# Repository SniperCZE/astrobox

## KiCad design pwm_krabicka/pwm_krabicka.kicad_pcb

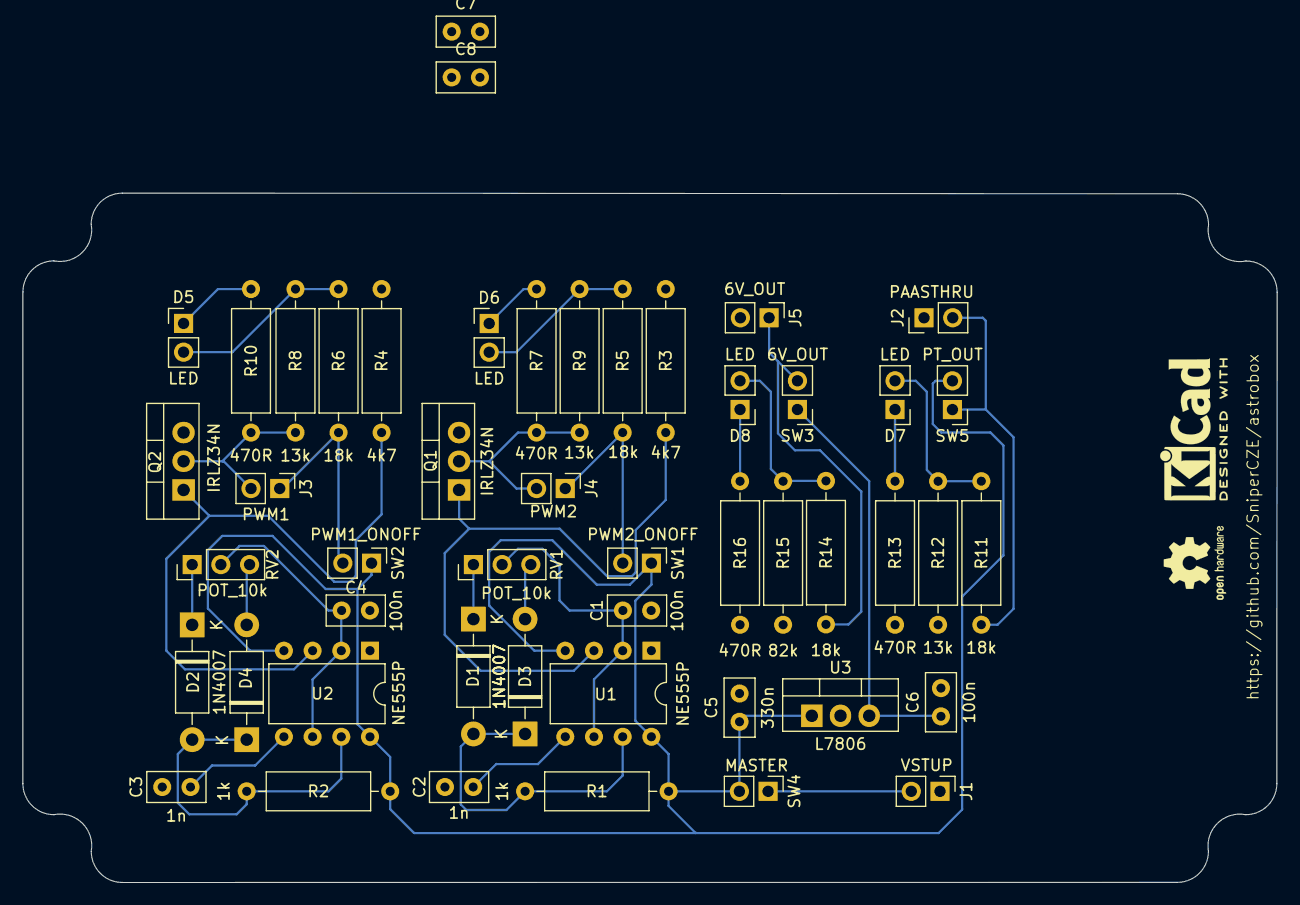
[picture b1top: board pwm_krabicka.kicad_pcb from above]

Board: 2 copper layers, 111.0 x 61.0 mm, 49 parts (0 on the bottom side), 30 nets.

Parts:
C1, C4, C6, C8: 100n; C_Disc_D5.0mm_W2.5mm_P2.50mm
C2, C3: 1n; C_Disc_D5.0mm_W2.5mm_P2.50mm
C5, C7: 330n; C_Disc_D5.0mm_W2.5mm_P2.50mm
D1, D2, D3, D4: 1N4007; D_DO-41_SOD81_P10.16mm_Horizontal
D5, D6, D7, D8: LED; PinHeader_1x02_P2.54mm_Vertical
J1: VSTUP; PinHeader_1x02_P2.54mm_Vertical
J2: PAASTHRU; PinHeader_1x02_P2.54mm_Vertical
J3: PWM1; PinHeader_1x02_P2.54mm_Vertical
J4: PWM2; PinHeader_1x02_P2.54mm_Vertical
J5: 6V_OUT; PinHeader_1x02_P2.54mm_Vertical
Q1, Q2: IRLZ34N; TO-220-3_Vertical
R1, R2: 1k; R_Axial_DIN0309_L9.0mm_D3.2mm_P12.70mm_Horizontal
R3, R4: 4k7; R_Axial_DIN0309_L9.0mm_D3.2mm_P12.70mm_Horizontal
R5, R6, R11, R14: 18k; R_Axial_DIN0309_L9.0mm_D3.2mm_P12.70mm_Horizontal
R7, R10, R13, R16: 470R; R_Axial_DIN0309_L9.0mm_D3.2mm_P12.70mm_Horizontal
R8, R9, R12: 13k; R_Axial_DIN0309_L9.0mm_D3.2mm_P12.70mm_Horizontal
R15: 82k; R_Axial_DIN0309_L9.0mm_D3.2mm_P12.70mm_Horizontal
RV1, RV2: POT_10k; PinHeader_1x03_P2.54mm_Vertical
SW1: PWM2_ONOFF; PinHeader_1x02_P2.54mm_Vertical
SW2: PWM1_ONOFF; PinHeader_1x02_P2.54mm_Vertical
SW3: 6V_OUT; PinHeader_1x02_P2.54mm_Vertical
SW4: MASTER; PinHeader_1x02_P2.54mm_Vertical
SW5: PT_OUT; PinHeader_1x02_P2.54mm_Vertical
U1, U2: NE555P; DIP-8_W7.62mm
U3: L7806; TO-220-3_Vertical

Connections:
/CGND1: C3.1, U2.5 (CV)
/CGND2: C2.1, U1.5 (CV)
/D1: D2.2 (A), D4.1 (K), R2.2, U2.7 (DIS)
/D2: D1.2 (A), D3.1 (K), R1.2, U1.7 (DIS)
/OUT1: Q2.1 (G), R4.1, U2.3 (Q)
/OUT2: Q1.1 (G), R3.1, U1.3 (Q)
/POT1: C4.1, RV2.2, U2.2 (TR), U2.6 (THR)
/POT2: C1.1, RV1.2, U1.2 (TR), U1.6 (THR)
/VCC1: C5.1, R1.1, R2.1, SW1.1 (A), SW2.1 (A), SW4.2 (B), SW5.2 (B), U1.4 (R), U1.8 (VCC), U2.4 (R), U2.8 (VCC), U3.1 (IN)
GND: C1.2, C2.2, C3.2, C4.2, C5.2, C6.2, J1.1, J2.1, J5.2, Q1.3 (S), Q2.3 (S), R3.2, R4.2, R12.2, R13.2, R15.1, R16.1, U1.1 (GND), U2.1 (GND), U3.2 (GND)
unnamed: D1.1 (K), RV1.1
unnamed: D2.1 (K), RV2.1
unnamed: D3.2 (A), RV1.3
unnamed: D4.2 (A), RV2.3
unnamed: D5.2 (A), R6.2, R8.1
unnamed: D5.1 (K), R10.1
unnamed: D6.2 (A), R5.2, R9.1
unnamed: D6.1 (K), R7.1
unnamed: D7.2 (A), R11.2, R12.1
unnamed: D7.1 (K), R13.1
unnamed: D8.2 (A), R14.2, R15.2
unnamed: D8.1 (K), R16.2
unnamed: J1.2, SW4.1 (A)
unnamed: J2.2, R11.1, SW5.1 (A)
unnamed: J3.1, R6.1, SW2.2 (B)
unnamed: J3.2, Q2.2 (D), R8.2, R10.2
unnamed: J4.1, R5.1, SW1.2 (B)
unnamed: J4.2, Q1.2 (D), R7.2, R9.2
unnamed: J5.1, R14.1, SW3.2 (B)
unnamed: C6.1, SW3.1 (A), U3.3 (OUT)
